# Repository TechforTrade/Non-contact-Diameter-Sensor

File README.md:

# Non-contact-Diameter-Sensor
Welcome to the Non-contact Diameter Sensor

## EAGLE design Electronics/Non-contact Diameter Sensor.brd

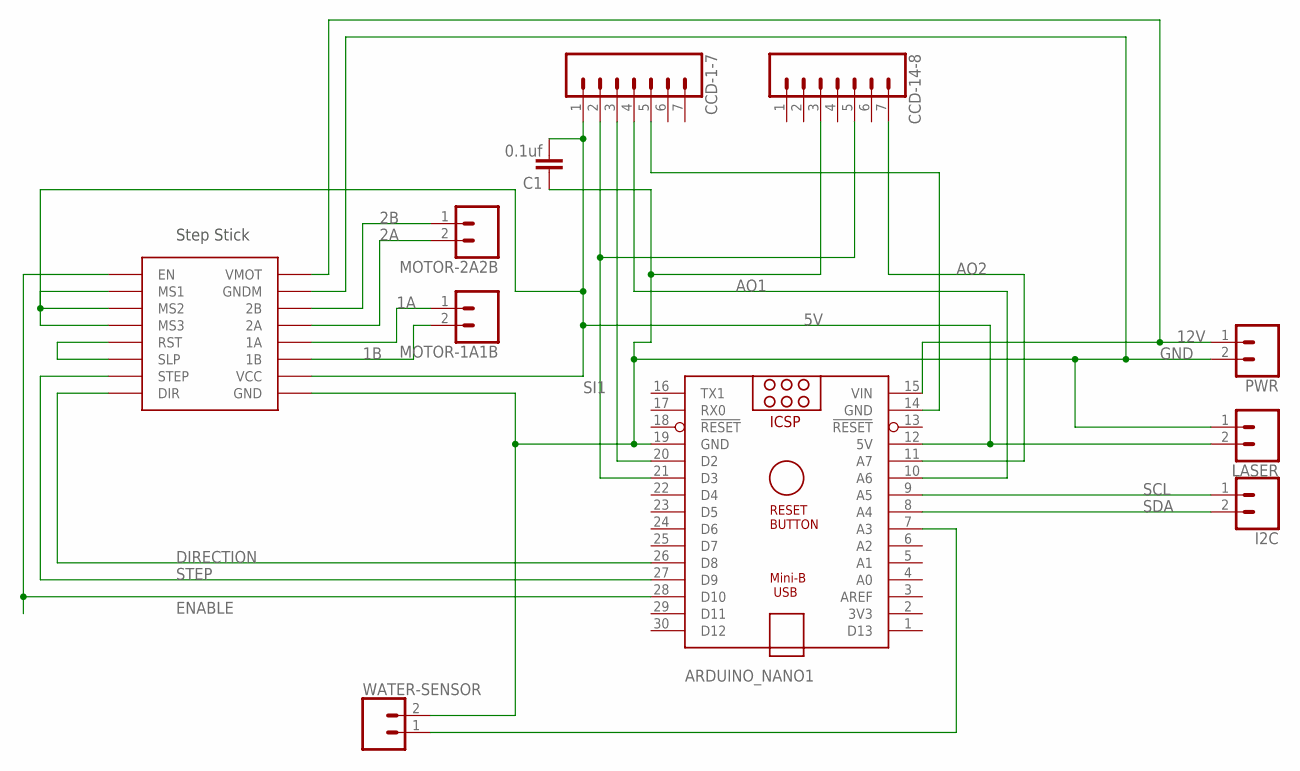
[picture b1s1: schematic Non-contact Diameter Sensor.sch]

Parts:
ARDUINO_NANO1: ARDUINO_NANO
C1: 0.1uf; C050-025X075
CCD-1-7, CCD-14-8: CONN_07; 1X07
I2C: CONN_023.5MM; SCREWTERMINAL-3.5MM-2
LASER: CONN_023.5MM; SCREWTERMINAL-3.5MM-2
MOTOR-1A1B, MOTOR-2A2B: CONN_023.5MM; SCREWTERMINAL-3.5MM-2
PWR: CONN_023.5MM; SCREWTERMINAL-3.5MM-2
U$1: STEP-STICK
WATER-SENSOR: CONN_02; 1X02

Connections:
1A: MOTOR-1A1B.1, U$1.1A
1B: MOTOR-1A1B.2, U$1.1B
2A: MOTOR-2A2B.2, U$1.2A
2B: MOTOR-2A2B.1, U$1.2B
5V: ARDUINO_NANO1.12 (5V), C1.2, CCD-1-7.1, LASER.2, U$1.MS1, U$1.MS2, U$1.MS3, U$1.VCC
12V: ARDUINO_NANO1.15 (VIN), PWR.1, U$1.VMOT
AO1: ARDUINO_NANO1.10 (A6), CCD-1-7.4
AO2: ARDUINO_NANO1.11 (A7), CCD-14-8.7
CLK: ARDUINO_NANO1.20 (D2), CCD-1-7.3
DIRECTION: ARDUINO_NANO1.26 (D8), U$1.DIR
ENABLE: ARDUINO_NANO1.28 (D10), U$1.EN
GND: ARDUINO_NANO1.14 (GND), ARDUINO_NANO1.19 (GND), C1.1, CCD-1-7.5, CCD-14-8.3, LASER.1, PWR.2, U$1.GND, U$1.GNDM, WATER-SENSOR.2
unnamed: ARDUINO_NANO1.7 (A3), WATER-SENSOR.1
unnamed: U$1.RST, U$1.SLP
SCL: ARDUINO_NANO1.9 (A5), I2C.1
SDA: ARDUINO_NANO1.8 (A4), I2C.2
SI1: ARDUINO_NANO1.21 (D3), CCD-1-7.2, CCD-14-8.5
STEP: ARDUINO_NANO1.27 (D9), U$1.SPT (STEP)

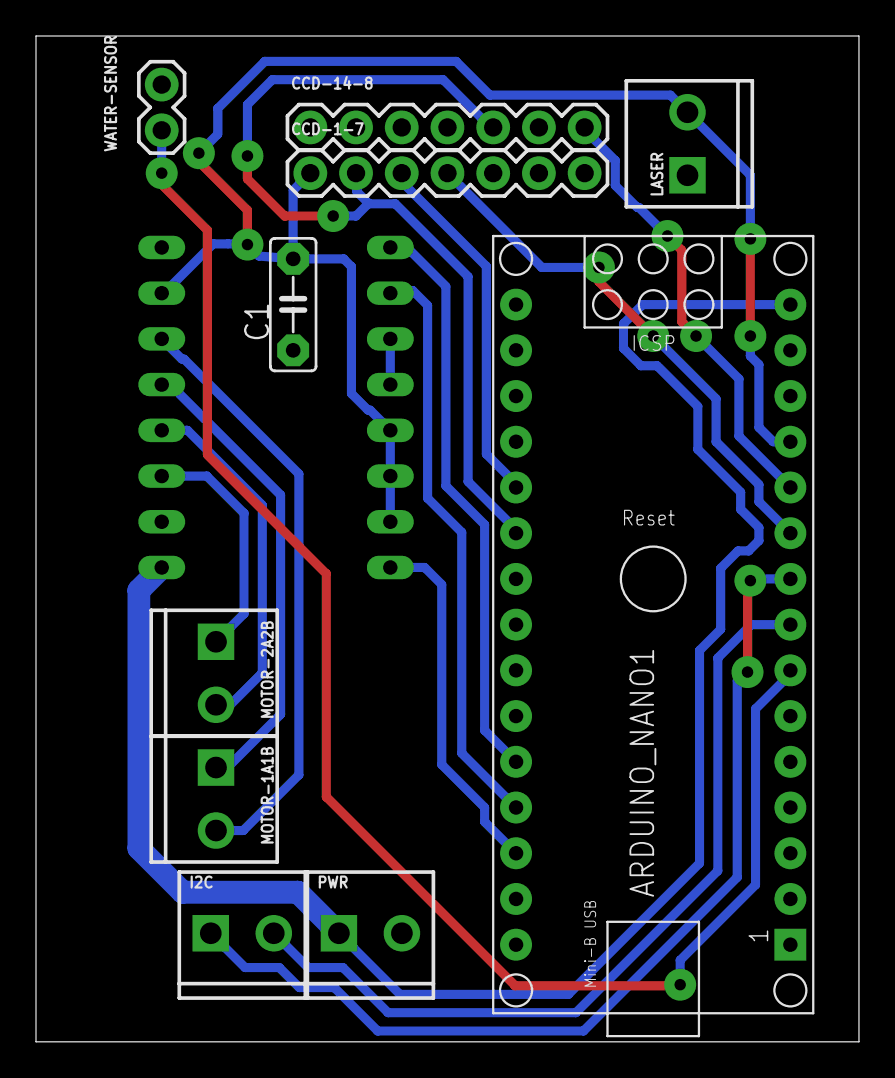
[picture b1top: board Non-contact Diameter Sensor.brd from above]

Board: 2 copper layers, 45.7 x 55.9 mm, 11 parts (0 on the bottom side), 18 nets.

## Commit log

2017-12-19 Initial Commit.
2018-12-17 Adding temp image.
2018-12-17 Adding images.
2018-12-17 fixing image name
2018-12-20 Added electronics files and restructured folders so that there is a Firmware and Electronics folder.
2018-12-21 Added arduino nano image
2018-12-21 Updating electronics images.
2018-12-21 Fixing images
2019-01-07 Adding image for wiki.
2019-01-28 Eliminated ground pour islands and reduced size of blank areas by moving traces. Moved J6 onto board a bit better.
2019-02-23 Redesigned the electronics board. Made the necessary changes in the pin assignments in the code. Updated image in the BOM.
2019-03-28 Reassigned pins in firmware to match new electronics board. Removed ability to turn laser on and off as the laser is no longer powered from a pin.
2019-03-28 Added branch for old pin out. Still testing...
2019-03-29 Added ability to use old or new pin configuration. Removed dead code from Diameter_Sensor_Calibration.ino. Added intro to how things work in the Diameter_Sensor_UI.pde file and fixed a few things.
2019-06-07 background correction as worked on in March

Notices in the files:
parts and their libraries:
SparkFun-Connectors: Licensing: Creative Commons ShareAlike 4.0 International - https://creativecommons.org/licenses/by-sa/4.0
